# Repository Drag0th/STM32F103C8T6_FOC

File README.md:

# STM32F103C8T6_FOC
STM32F103C8T6_FOC is an open-source project designed for controlling NEMA 17 stepper motors using Field Oriented Control (FOC). It is based on the STM32F103C8T6 microcontroller and provides a reference PCB for building a precise and smooth stepper motor controller. The project is aimed at hobbyists and developers who want to drive NEMA 17 motors efficiently for applications like CNC machines, 3D printers, or robotic systems.

# :floppy_disk: Firmware
**WORK IN PROGRESS**

# :file_folder: References, Links and Notes
- [STM32F103C8T6 Datasheet](https://github.com/Drag0th/STM32F103C8T6_FOC/blob/main/Documentation/stm32f103c8.pdf)
- [SN65HVD230 Datasheet](https://github.com/Drag0th/STM32F103C8T6_FOC/blob/main/Documentation/sn65hvd230.pdf)
- [TMC2209 Datasheet](https://github.com/Drag0th/STM32F103C8T6_FOC/blob/main/Documentation/tmc2209_datasheet_rev1.09.pdf)
- [M24C64-F Datasheet](https://github.com/Drag0th/STM32F103C8T6_FOC/blob/main/Documentation/m24c64-f.pdf)
- [BD9E303EFJ-LB Datasheet](https://github.com/Drag0th/STM32F103C8T6_FOC/blob/main/Documentation/bd9e303efj-lb-e.pdf)
- [AS5600 Datasheet](https://github.com/Drag0th/STM32F103C8T6_FOC/blob/main/Documentation/AS5600.pdf)

# :page_facing_up: License
*All hardware designs are released under the CERN-OHL-P v2 license.*

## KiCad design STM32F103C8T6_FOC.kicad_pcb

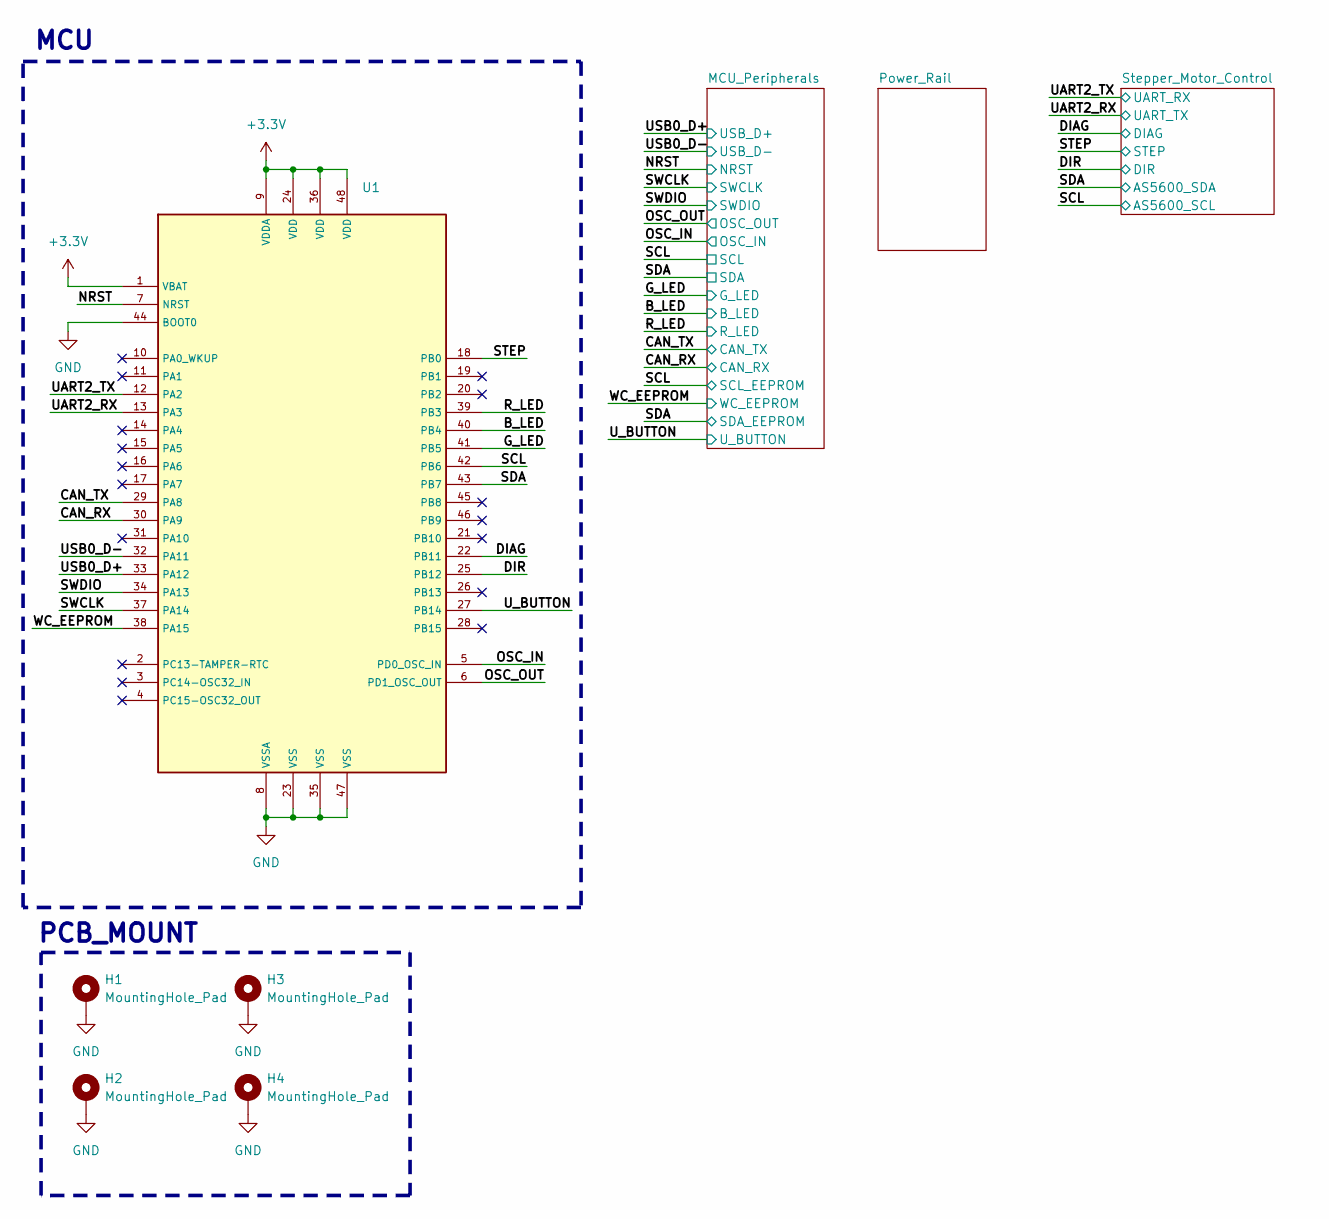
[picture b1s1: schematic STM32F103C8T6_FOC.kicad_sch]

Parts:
H1, H2, H3, H4: MountingHole_Pad; MountingHole_3.2mm_M3_ISO7380_Pad
U1: QFP50P900X900X160-48N

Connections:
+3.3V: U1.1 (VBAT), U1.9 (VDDA), U1.24 (VDD), U1.36 (VDD), U1.48 (VDD); also elsewhere on the board
/B_LED: U1.40 (PB4); also elsewhere on the board
/CAN_RX: U1.46 (PB9); also elsewhere on the board
/CAN_TX: U1.45 (PB8); also elsewhere on the board
/DIAG: U1.22 (PB11); also elsewhere on the board
/DIR: U1.25 (PB12); also elsewhere on the board
/G_LED: U1.41 (PB5); also elsewhere on the board
/NRST: U1.7 (NRST); also elsewhere on the board
/OSC_IN: U1.5 (PD0_OSC_IN); also elsewhere on the board
/OSC_OUT: U1.6 (PD1_OSC_OUT); also elsewhere on the board
/R_LED: U1.39 (PB3); also elsewhere on the board
/SCL: U1.42 (PB6); also elsewhere on the board
/SDA: U1.43 (PB7); also elsewhere on the board
/STEP: U1.18 (PB0); also elsewhere on the board
/SWCLK: U1.37 (PA14); also elsewhere on the board
/SWDIO: U1.34 (PA13); also elsewhere on the board
/UART2_RX: U1.13 (PA3); also elsewhere on the board
/UART2_TX: U1.12 (PA2); also elsewhere on the board
/USB0_D+: U1.33 (PA12); also elsewhere on the board
/USB0_D-: U1.32 (PA11); also elsewhere on the board
/U_BUTTON: U1.27 (PB14); also elsewhere on the board
/WC_EEPROM: U1.38 (PA15); also elsewhere on the board
GND: H1.1, H2.1, H3.1, H4.1, U1.8 (VSSA), U1.23 (VSS), U1.35 (VSS), U1.44 (BOOT0), U1.47 (VSS); also elsewhere on the board

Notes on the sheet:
PCB_MOUNT
MCU

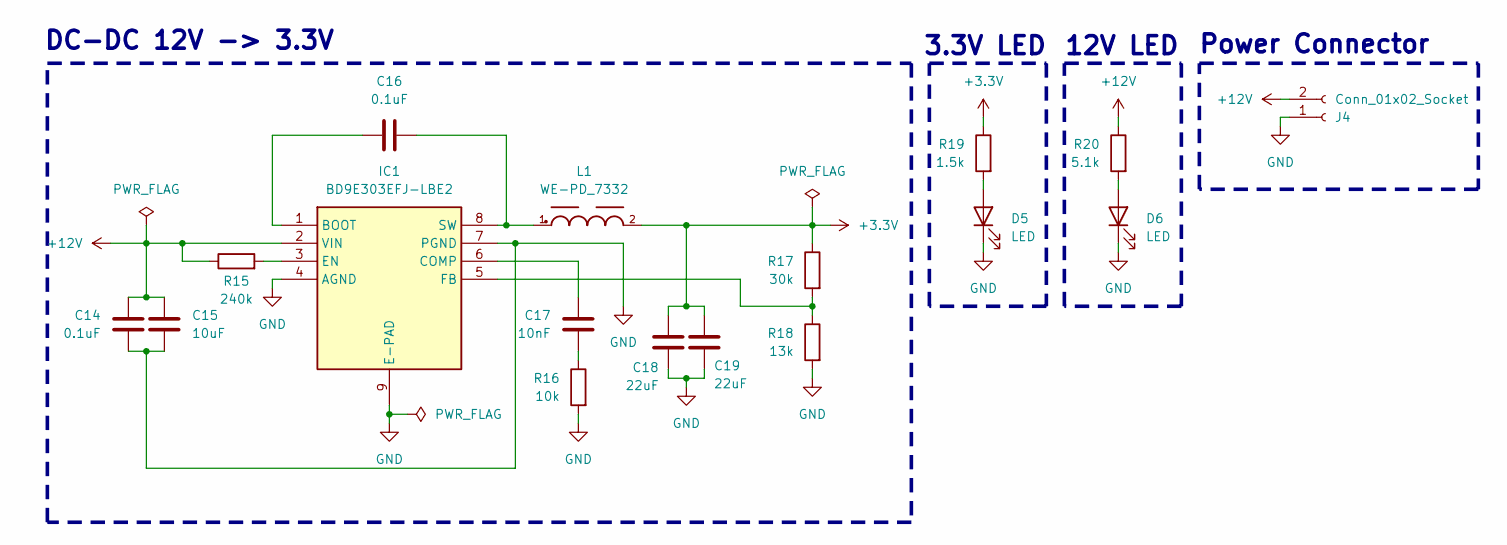
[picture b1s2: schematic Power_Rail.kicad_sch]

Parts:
C14, C16: 0.1uF; C_0402_1005Metric_Pad0.74x0.62mm_HandSolder
C15: 10uF; C_0402_1005Metric_Pad0.74x0.62mm_HandSolder
C17: 10nF; C_0402_1005Metric_Pad0.74x0.62mm_HandSolder
C18, C19: 22uF; C_0402_1005Metric_Pad0.74x0.62mm_HandSolder
D5, D6: LED; LED_0603_1608Metric_Pad1.05x0.95mm_HandSolder
IC1: BD9E303EFJ-LBE2; SOIC127P600X100-9N; Mouser Part Number 755-BD9E303EFJ-LBE2
J4: Conn_01x02_Socket; JST_PH_S2B-PH-K_1x02_P2.00mm_Horizontal
L1: WE-PD_7332
R15: 240k; R_0603_1608Metric_Pad0.98x0.95mm_HandSolder
R16: 10k; R_0402_1005Metric_Pad0.72x0.64mm_HandSolder
R17: 30k; R_0402_1005Metric_Pad0.72x0.64mm_HandSolder
R18: 13k; R_0402_1005Metric_Pad0.72x0.64mm_HandSolder
R19: 1.5k; R_0402_1005Metric_Pad0.72x0.64mm_HandSolder
R20: 5.1k; R_0402_1005Metric_Pad0.72x0.64mm_HandSolder

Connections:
+3.3V: C18.2, C19.2, L1.2, R17.1, R19.1; also elsewhere on the board
+12V: C14.2, C15.2, IC1.2 (VIN), J4.2, R15.1, R20.1; also elsewhere on the board
GND: C14.1, C15.1, C18.1, C19.1, D5.1 (K), D6.1 (K), IC1.4 (AGND), IC1.7 (PGND), IC1.9 (E-PAD), J4.1, R16.2, R18.2; also elsewhere on the board
unnamed: C17.1, R16.1
unnamed: D5.2 (A), R19.2
unnamed: D6.2 (A), R20.2
unnamed: C16.1, IC1.1 (BOOT)
unnamed: C17.2, IC1.6 (COMP)
unnamed: IC1.3 (EN), R15.2
unnamed: IC1.5 (FB), R17.2, R18.1
unnamed: C16.2, IC1.8 (SW), L1.1

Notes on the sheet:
12V LED
DC-DC 12V -> 3.3V
Power Connector
3.3V LED

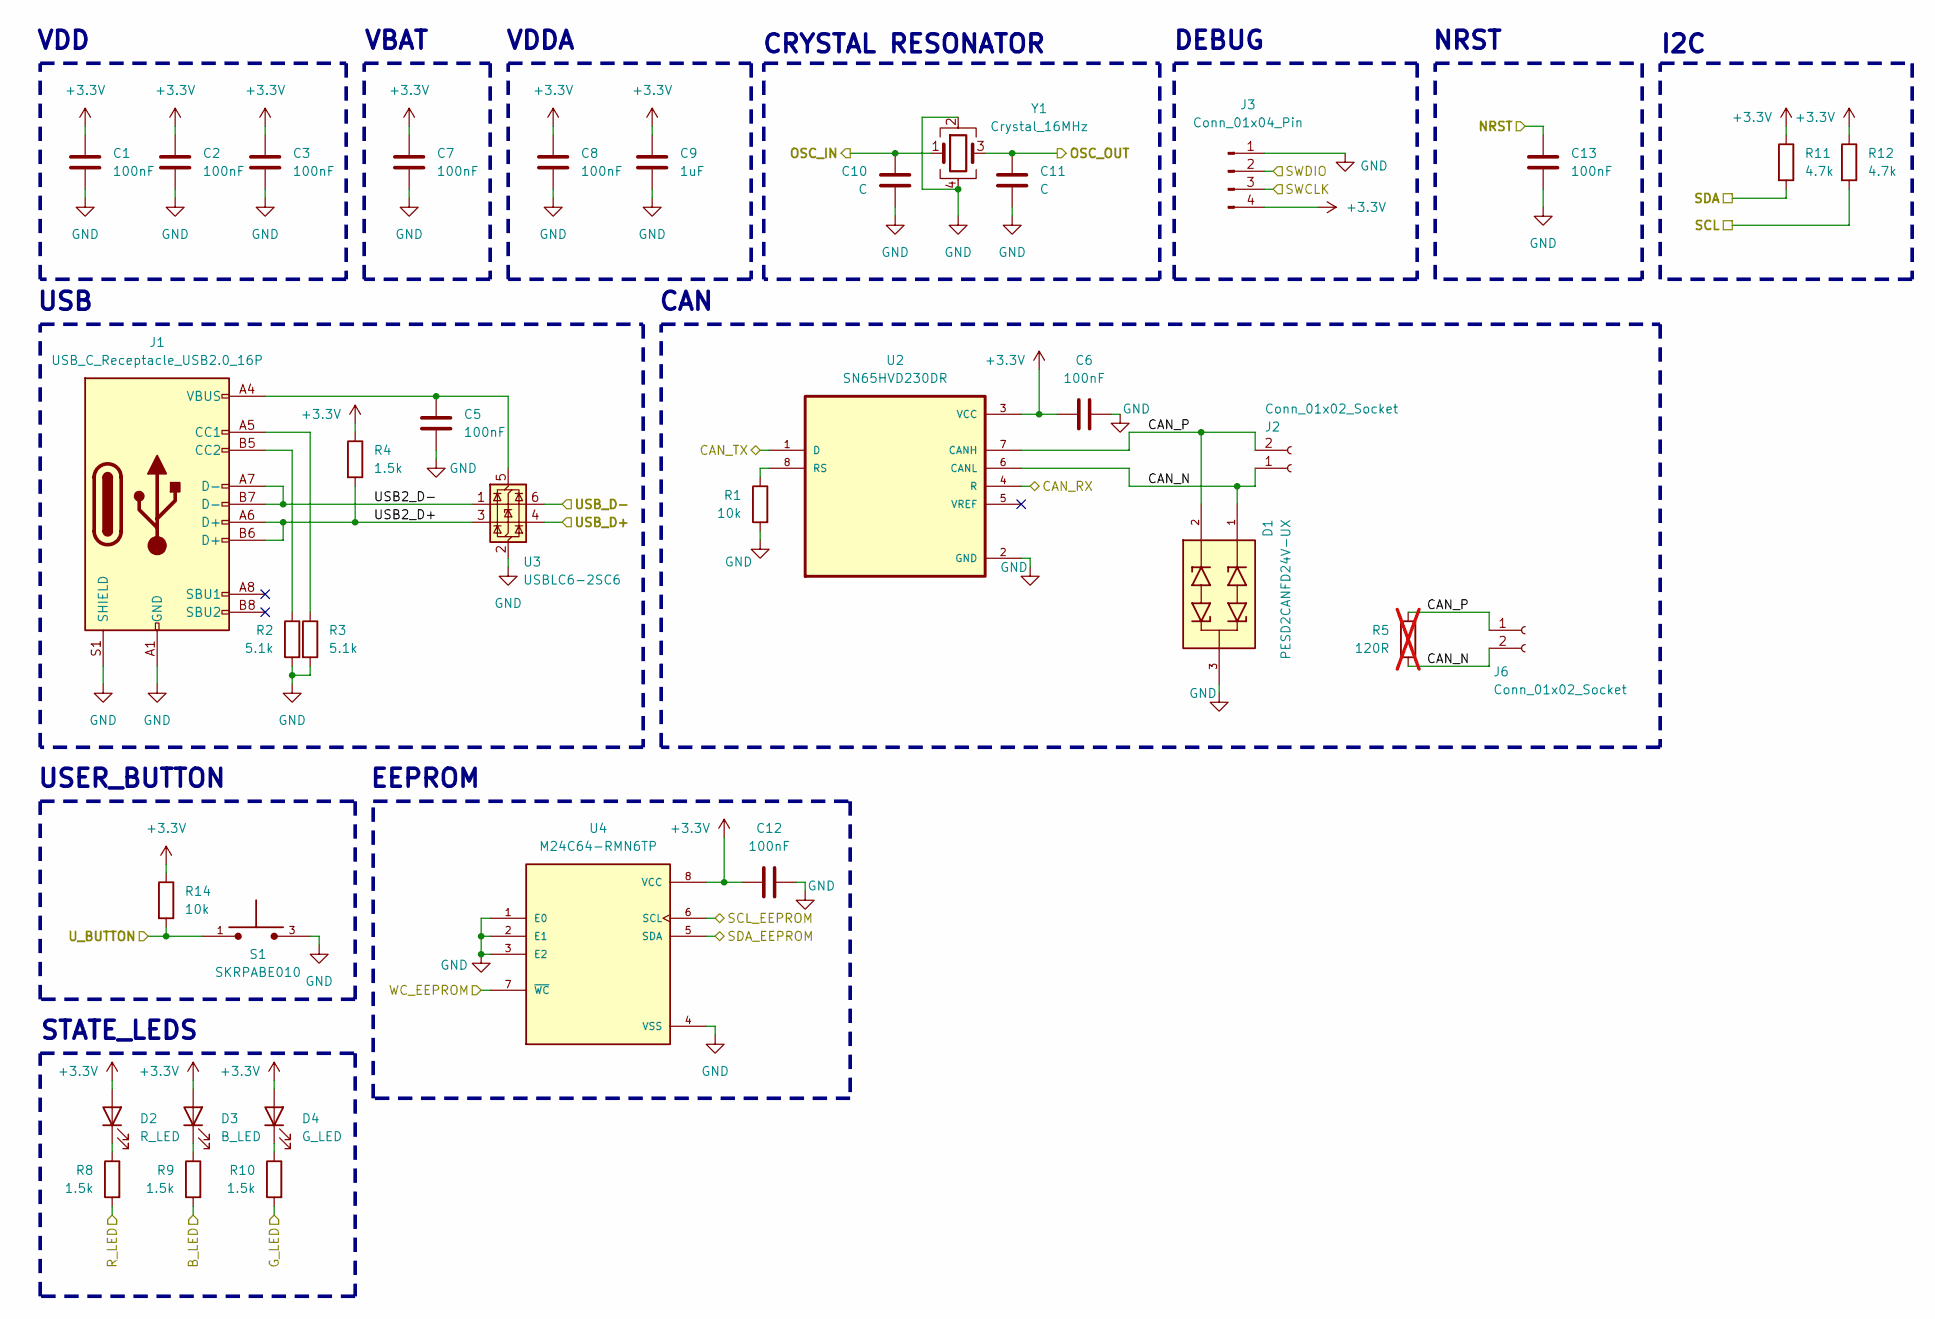
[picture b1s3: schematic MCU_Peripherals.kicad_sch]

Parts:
C1, C2, C3, C5, C6, C7, C8, C12, C13: 100nF; C_0402_1005Metric_Pad0.74x0.62mm_HandSolder
C9: 1uF; C_0402_1005Metric_Pad0.74x0.62mm_HandSolder
C10, C11: C; C_0402_1005Metric_Pad0.74x0.62mm_HandSolder
D1: PESD2CANFD24V-UX; TVS_PESD2CANFD24V-UX; PARTREV V.4
D2: R_LED; LED_0603_1608Metric_Pad1.05x0.95mm_HandSolder
D3: B_LED; LED_0603_1608Metric_Pad1.05x0.95mm_HandSolder
D4: G_LED; LED_0603_1608Metric_Pad1.05x0.95mm_HandSolder
J1: USB_C_Receptacle_USB2.0_16P; USB_C_Receptacle_HRO_TYPE-C-31-M-12
J2, J6: Conn_01x02_Socket; JST_PH_S2B-PH-K_1x02_P2.00mm_Horizontal
J3: Conn_01x04_Pin; PinHeader_1x04_P2.54mm_Vertical
R1, R14: 10k; R_0402_1005Metric_Pad0.72x0.64mm_HandSolder
R2, R3: 5.1k; R_0402_1005Metric_Pad0.72x0.64mm_HandSolder
R4, R8, R9, R10: 1.5k; R_0402_1005Metric_Pad0.72x0.64mm_HandSolder
R5: 120R; R_0402_1005Metric_Pad0.72x0.64mm_HandSolder; not fitted
R11, R12: 4.7k; R_0402_1005Metric_Pad0.72x0.64mm_HandSolder
S1: SKRPABE010; SW_SKRPABE010
U2: SN65HVD230DR; SOIC127P599X175-8N
U3: USBLC6-2SC6; SOT-23-6
U4: M24C64-RMN6TP; SOIC127P600X175-8N; PARTREV 38
Y1: Crystal_16MHz; Crystal_SMD_3225-4Pin_3.2x2.5mm_HandSoldering

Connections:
+3.3V: C1.1, C2.1, C3.1, C6.1, C7.1, C8.1, C9.1, C12.1, D2.2 (A), D3.2 (A), D4.2 (A), J3.4, R4.1, R11.1, R12.1, R14.1, U2.3 (VCC), U4.8 (VCC); also elsewhere on the board
/B_LED: R9.2; also elsewhere on the board
/CAN_RX: U2.4 (R); also elsewhere on the board
/CAN_TX: U2.1 (D); also elsewhere on the board
/G_LED: R10.2; also elsewhere on the board
/MCU_Peripherals/CAN_N: D1.1, J2.1, J6.2, R5.2, U2.6 (CANL)
/MCU_Peripherals/CAN_P: D1.2, J2.2, J6.1, R5.1, U2.7 (CANH)
/MCU_Peripherals/USB2_D+: J1.A6 (D+), J1.B6 (D+), R4.2, U3.3 (I/O2)
/MCU_Peripherals/USB2_D-: J1.A7 (D-), J1.B7 (D-), U3.1 (I/O1)
/NRST: C13.1; also elsewhere on the board
/OSC_IN: C10.1, Y1.1; also elsewhere on the board
/OSC_OUT: C11.1, Y1.3; also elsewhere on the board
/R_LED: R8.2; also elsewhere on the board
/SCL: R12.2, U4.6 (SCL); also elsewhere on the board
/SDA: R11.2, U4.5 (SDA); also elsewhere on the board
/SWCLK: J3.3; also elsewhere on the board
/SWDIO: J3.2; also elsewhere on the board
/USB0_D+: U3.4 (I/O2); also elsewhere on the board
/USB0_D-: U3.6 (I/O1); also elsewhere on the board
/U_BUTTON: R14.2, S1.1, S1.2; also elsewhere on the board
/WC_EEPROM: U4.7 (~WC); also elsewhere on the board
GND: C1.2, C2.2, C3.2, C5.2, C6.2, C7.2, C8.2, C9.2, C10.2, C11.2, C12.2, C13.2, D1.3, J1.A1 (GND), J1.A12 (GND), J1.B1 (GND), J1.B12 (GND), J1.S1 (SHIELD), J3.1, R1.2, R2.2, R3.2, S1.3, S1.4, U2.2 (GND), U3.2 (GND), U4.1 (E0), U4.2 (E1), U4.3 (E2), U4.4 (VSS), Y1.2, Y1.4; also elsewhere on the board
unnamed: D2.1 (K), R8.1
unnamed: D3.1 (K), R9.1
unnamed: D4.1 (K), R10.1
unnamed: J1.A5 (CC1), R3.1
unnamed: J1.B5 (CC2), R2.1
unnamed: R1.1, U2.8 (RS)
unnamed: C5.1, J1.A4 (VBUS), J1.A9 (VBUS), J1.B4 (VBUS), J1.B9 (VBUS), U3.5 (VBUS)

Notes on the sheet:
VDDA
CRYSTAL RESONATOR
CAN
EEPROM
VDD
STATE_LEDS
DEBUG
NRST
VBAT
USER_BUTTON
I2C
USB

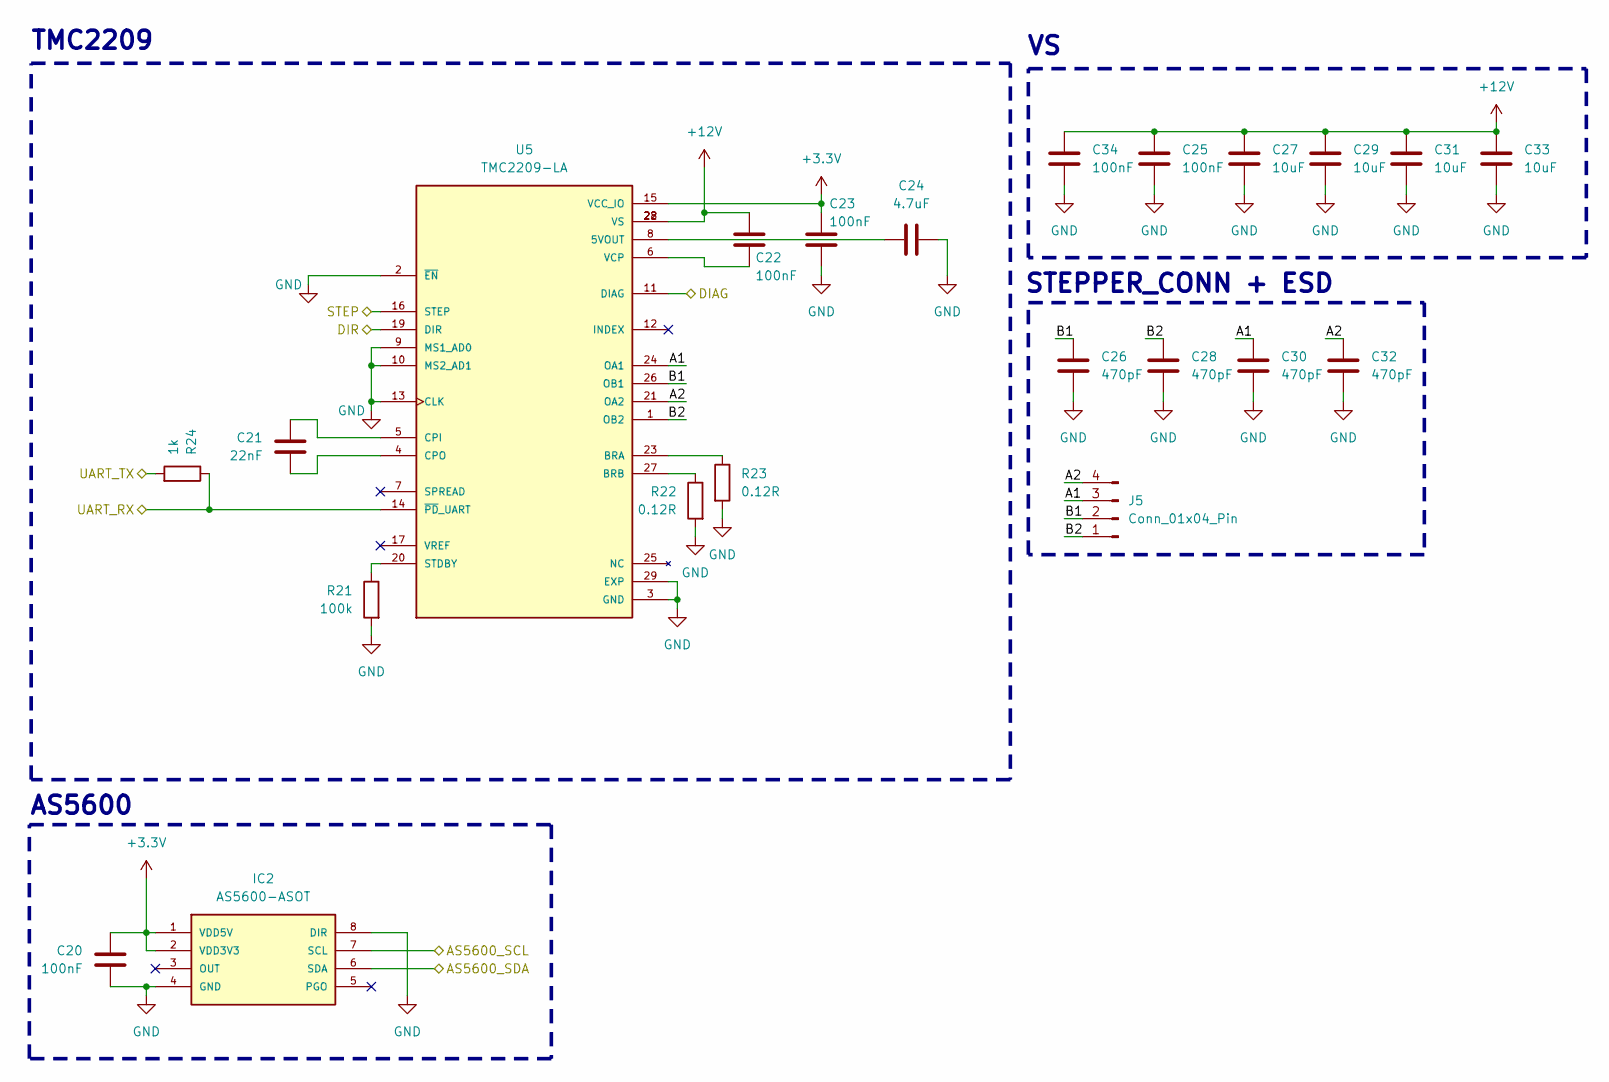
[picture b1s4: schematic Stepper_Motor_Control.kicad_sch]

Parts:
C20, C22, C23, C25, C34: 100nF; C_0402_1005Metric_Pad0.74x0.62mm_HandSolder
C21: 22nF; C_0402_1005Metric_Pad0.74x0.62mm_HandSolder
C24: 4.7uF; C_0402_1005Metric_Pad0.74x0.62mm_HandSolder
C26, C28, C30, C32: 470pF; C_0402_1005Metric_Pad0.74x0.62mm_HandSolder
C27, C29, C31, C33: 10uF; C_0603_1608Metric_Pad1.08x0.95mm_HandSolder
IC2: AS5600-ASOT; SOIC127P600X175-8N; MOUSER_PART_NUMBER 985-AS5600-ASOT
J5: Conn_01x04_Pin; JST_PH_S4B-PH-K_1x04_P2.00mm_Horizontal
R21: 100k; R_0402_1005Metric_Pad0.72x0.64mm_HandSolder
R22, R23: 0.12R; R_2010_5025Metric_Pad1.40x2.65mm_HandSolder
R24: 1k; R_0402_1005Metric_Pad0.72x0.64mm_HandSolder
U5: TMC2209-LA; QFN50P500X500X90-29N; PARTREV 1.08

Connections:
+3.3V: C20.1, C23.1, IC2.1 (VDD5V), IC2.2 (VDD3V3), U5.15 (VCC_IO); also elsewhere on the board
+12V: C22.1, C25.1, C27.1, C29.1, C31.1, C33.1, C34.1, U5.22 (VS), U5.28 (VS); also elsewhere on the board
/DIAG: U5.11 (DIAG); also elsewhere on the board
/DIR: U5.19 (DIR); also elsewhere on the board
/SCL: IC2.7 (SCL); also elsewhere on the board
/SDA: IC2.6 (SDA); also elsewhere on the board
/STEP: U5.16 (STEP); also elsewhere on the board
/Stepper_Motor_Control/A1: C30.1, J5.3, U5.24 (OA1)
/Stepper_Motor_Control/A2: C32.1, J5.4, U5.21 (OA2)
/Stepper_Motor_Control/B1: C26.1, J5.2, U5.26 (OB1)
/Stepper_Motor_Control/B2: C28.1, J5.1, U5.1 (OB2)
/UART2_RX: R24.2; also elsewhere on the board
/UART2_TX: R24.1, U5.14 (~PD_UART); also elsewhere on the board
GND: C20.2, C23.2, C24.2, C25.2, C26.2, C27.2, C28.2, C29.2, C30.2, C31.2, C32.2, C33.2, C34.2, IC2.4 (GND), IC2.8 (DIR), R21.2, R22.2, R23.2, U5.2 (~EN), U5.3 (GND), U5.9 (MS1_AD0), U5.10 (MS2_AD1), U5.13 (CLK), U5.18 (GND), U5.29 (EXP); also elsewhere on the board
unnamed: C24.1, U5.8 (5VOUT)
unnamed: R23.1, U5.23 (BRA)
unnamed: R22.1, U5.27 (BRB)
unnamed: C21.1, U5.5 (CPI)
unnamed: C21.2, U5.4 (CPO)
unnamed: R21.1, U5.20 (STDBY)
unnamed: C22.2, U5.6 (VCP)

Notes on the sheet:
TMC2209
STEPPER_CONN + ESD
AS5600

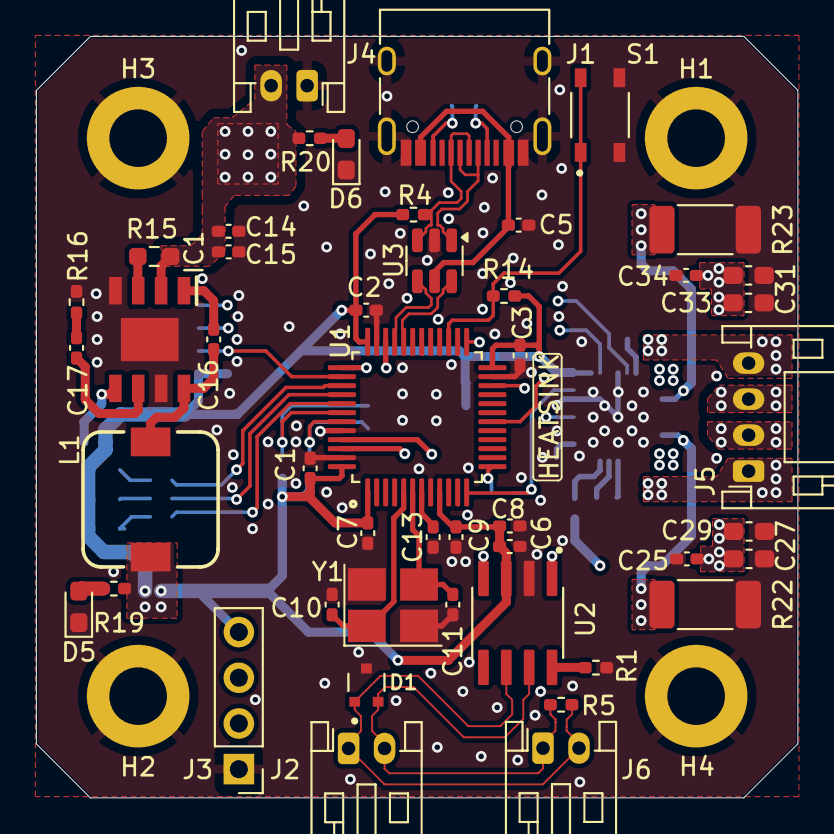
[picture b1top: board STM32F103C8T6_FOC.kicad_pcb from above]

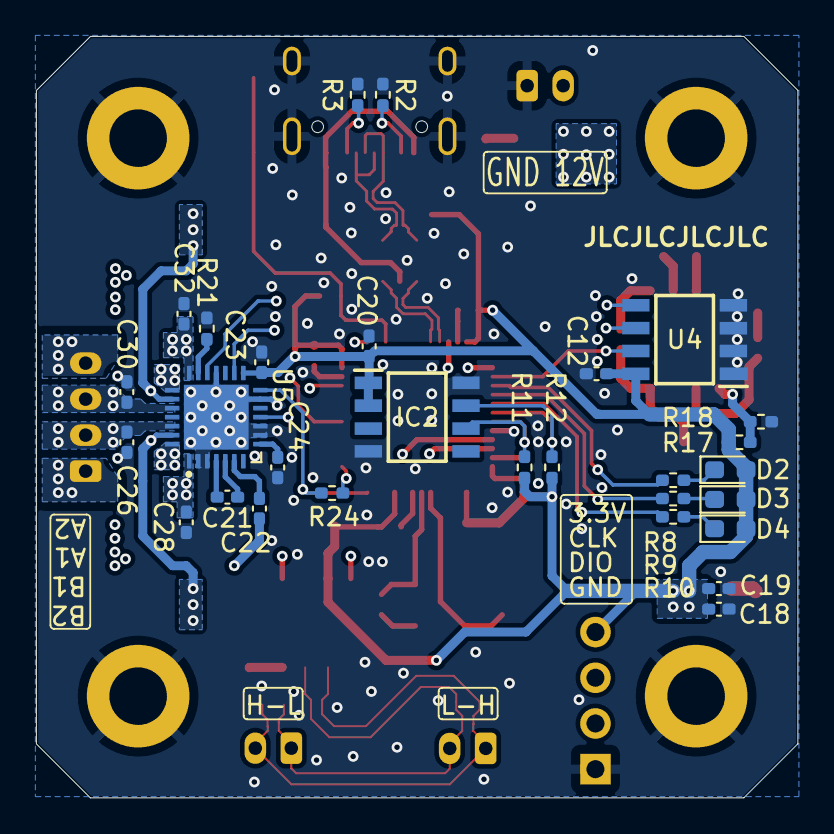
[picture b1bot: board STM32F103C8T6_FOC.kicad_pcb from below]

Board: 4 copper layers, 42.3 x 42.3 mm, 80 parts (29 on the bottom side), 54 nets.

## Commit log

2025-12-10 Power Rail Update
2025-12-15 TMC2209 Update
2025-12-19 Stepper Motor Control Update
2025-12-21 CAN & EEPROM Update
2025-12-25 LEDs, Button & Small fixes
2025-12-26 Schematic finish & ERC
2025-12-26 Footprint Update
2025-12-28 Layout Update
2026-01-03 Schematic check, Text adjustment & QoL changes
2026-01-08 Constrains & Check
2026-01-14 Repo Cleanup
2026-01-14 Create LICENSE
2026-01-24 Heatsink Fix
